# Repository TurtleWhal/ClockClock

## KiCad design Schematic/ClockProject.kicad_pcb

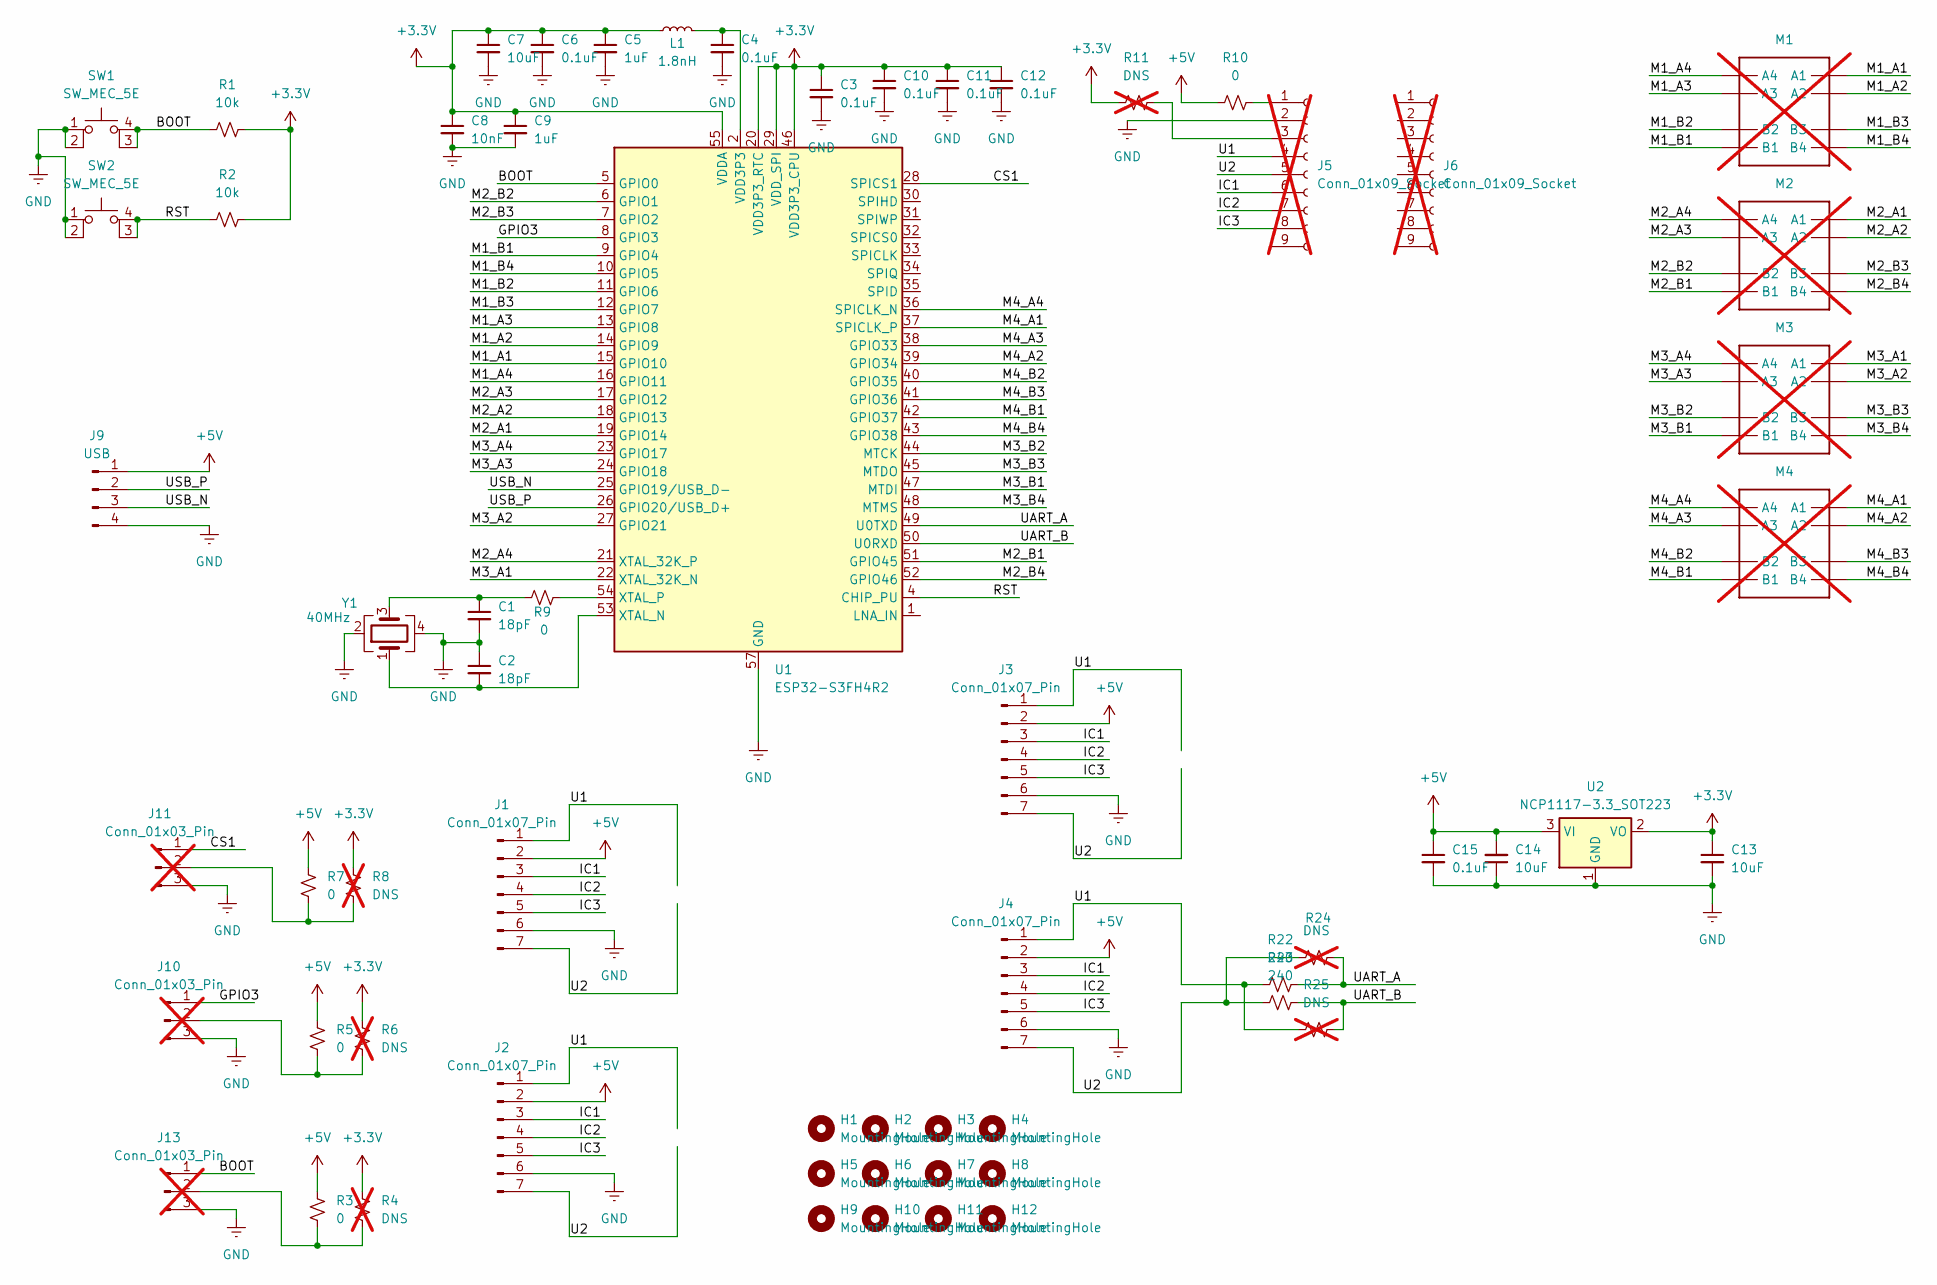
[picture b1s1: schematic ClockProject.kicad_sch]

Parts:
C1, C2: 18pF; C_0805_2012Metric; LCSC Part # C1797
C3, C4, C6, C10, C11, C12, C15: 0.1uF; C_0805_2012Metric; LCSC Part # C49678
C5, C9: 1uF; C_0805_2012Metric; LCSC Part # C28323
C7, C13, C14: 10uF; C_0805_2012Metric; LCSC Part # C15850
C8: 10nF; C_0805_2012Metric; LCSC Part # C1710
H1, H2, H3, H4, H5, H6, H7, H8, H9, H10, H11, H12: MountingHole; MountingHole_3.5mm
J1, J2: Conn_01x07_Pin; HDR-SMD_7P-P2.54-H-F-L11.5; LCSC Part # C5142240
J3, J4: Conn_01x07_Pin; HDR-SMD_7P-P2.54-H-F-L11.5-RIGHT; LCSC Part # C5142240
J5, J6: Conn_01x09_Socket; PinSocket_1x09_P2.54mm_Vertical; not fitted
J9: USB; PinHeader_1x04_P2.54mm_Vertical_SMD_Pin1Right; LCSC Part # C2984276
J10, J11, J13: Conn_01x03_Pin; PinSocket_1x03_P2.54mm_Vertical; not fitted
L1: 1.8nH; L_0805_2012Metric; LCSC Part # C1036
M1, M2, M3, M4: VID28-05; not fitted
R1, R2: 10k; R_0805_2012Metric; LCSC Part # C17414
R3, R5, R7, R9, R10: 0; R_0805_2012Metric; LCSC Part # C17477
R4, R6, R8, R24, R25: DNS; R_0805_2012Metric; not fitted
R11: DNS; R_0805_2012Metric; LCSC Part # C17572; not fitted
R22, R23: 240; R_0805_2012Metric; LCSC Part # C17572
SW1, SW2: SW_MEC_5E; SW-SMD_4P-L5.1-W5.1-P3.70-LS6.5-TL_H1.5; LCSC Part # C318884
U1: ESP32-S3FH4R2; QFN56_S3FH4R2_EXP; LCSC Part # C3013940
U2: NCP1117-3.3_SOT223; SOT-223-3_TabPin2; LCSC Part # C6186
Y1: 40MHz; Crystal_SMD_TXC_7M-4Pin_3.2x2.5mm; LCSC Part # C19191260

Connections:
+3.3V: C3.1, C5.1, C6.1, C7.1, C8.1, C9.1, C10.1, C11.1, C12.1, C13.1, L1.1, R1.2, R2.2, R4.2, R6.2, R8.2, R11.2, U1.20 (VDD3P3_RTC), U1.29 (VDD_SPI), U1.46 (VDD3P3_CPU), U1.55 (VDDA), U1.56 (VDDA), U2.2 (VO)
+5V: C14.2, C15.1, J1.2, J2.2, J3.2, J4.2, J9.1, R3.2, R5.2, R7.2, R10.2, U2.3 (VI)
/BOOT: J13.1, R1.1, SW1.3 (K), SW1.4 (A), U1.5 (GPIO0)
/CS1: J11.1, U1.28 (SPICS1)
/GPIO3: J10.1, U1.8 (GPIO3)
/IC1: J1.3, J2.3, J3.3, J4.3, J5.6
/IC2: J1.4, J2.4, J3.4, J4.4, J5.7
/IC3: J1.5, J2.5, J3.5, J4.5, J5.8
/M1_A1: M1.A1, U1.15 (GPIO10)
/M1_A2: M1.A2, U1.14 (GPIO9)
/M1_A3: M1.A3, U1.13 (GPIO8)
/M1_A4: M1.A4, U1.16 (GPIO11)
/M1_B1: M1.B1, U1.9 (GPIO4)
/M1_B2: M1.B2, U1.11 (GPIO6)
/M1_B3: M1.B3, U1.12 (GPIO7)
/M1_B4: M1.B4, U1.10 (GPIO5)
/M2_A1: M2.A1, U1.19 (GPIO14)
/M2_A2: M2.A2, U1.18 (GPIO13)
/M2_A3: M2.A3, U1.17 (GPIO12)
/M2_A4: M2.A4, U1.21 (XTAL_32K_P)
/M2_B1: M2.B1, U1.51 (GPIO45)
/M2_B2: M2.B2, U1.6 (GPIO1)
/M2_B3: M2.B3, U1.7 (GPIO2)
/M2_B4: M2.B4, U1.52 (GPIO46)
/M3_A1: M3.A1, U1.22 (XTAL_32K_N)
/M3_A2: M3.A2, U1.27 (GPIO21)
/M3_A3: M3.A3, U1.24 (GPIO18)
/M3_A4: M3.A4, U1.23 (GPIO17)
/M3_B1: M3.B1, U1.47 (MTDI)
/M3_B2: M3.B2, U1.44 (MTCK)
/M3_B3: M3.B3, U1.45 (MTDO)
/M3_B4: M3.B4, U1.48 (MTMS)
/M4_A1: M4.A1, U1.37 (SPICLK_P)
/M4_A2: M4.A2, U1.39 (GPIO34)
/M4_A3: M4.A3, U1.38 (GPIO33)
/M4_A4: M4.A4, U1.36 (SPICLK_N)
/M4_B1: M4.B1, U1.42 (GPIO37)
/M4_B2: M4.B2, U1.40 (GPIO35)
/M4_B3: M4.B3, U1.41 (GPIO36)
/M4_B4: M4.B4, U1.43 (GPIO38)
/RST: R2.1, SW2.3 (K), SW2.4 (A), U1.4 (CHIP_PU)
/U1: J1.1, J2.1, J3.1, J4.1, J5.4, R22.2, R25.2
/U2: J1.7, J2.7, J3.7, J4.7, J5.5, R23.2, R24.2
/UART_A: R22.1, R24.1, U1.49 (U0TXD)
/UART_B: R23.1, R25.1, U1.50 (U0RXD)
/USB_N: J9.3, U1.25 (GPIO19/USB_D-)
/USB_P: J9.2, U1.26 (GPIO20/USB_D+)
GND: C1.2, C2.1, C3.2, C4.2, C5.2, C6.2, C7.2, C8.2, C9.2, C10.2, C11.2, C12.2, C13.2, C14.1, C15.2, J1.6, J2.6, J3.6, J4.6, J5.2, J9.4, J10.3, J11.3, J13.3, SW1.1, SW1.2, SW2.1, SW2.2, U1.57 (GND), U2.1 (GND), Y1.2, Y1.4
unnamed: C1.1, R9.2, Y1.3
unnamed: C4.1, L1.2, U1.2 (VDD3P3), U1.3 (VDD3P3)
unnamed: J5.1, R10.1
unnamed: J5.3, R11.1
unnamed: J10.2, R5.1, R6.1
unnamed: J11.2, R7.1, R8.1
unnamed: J13.2, R3.1, R4.1
unnamed: C2.2, U1.53 (XTAL_N), Y1.1
unnamed: R9.1, U1.54 (XTAL_P)

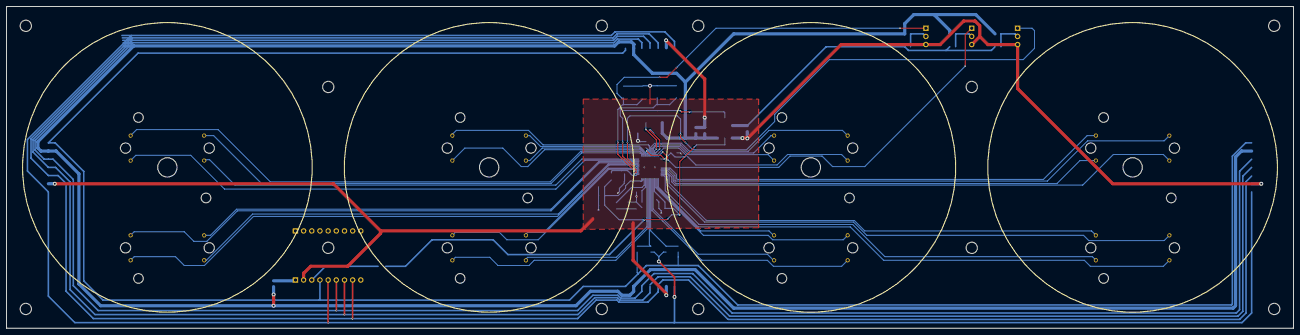
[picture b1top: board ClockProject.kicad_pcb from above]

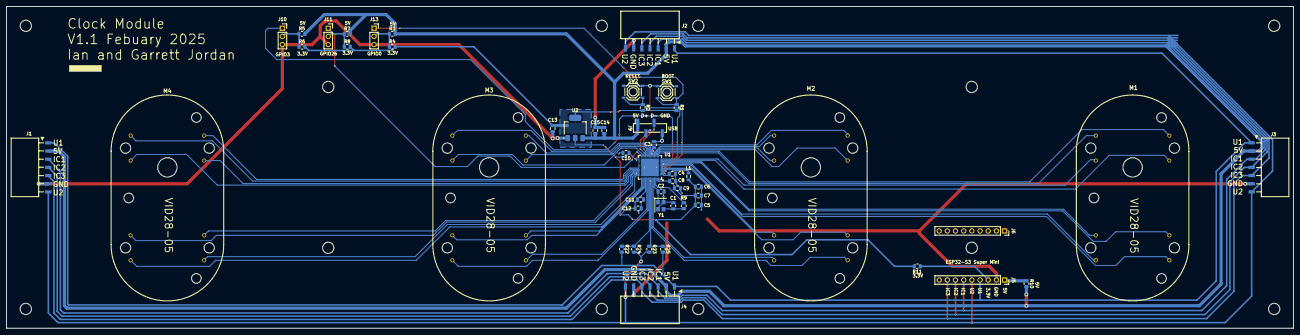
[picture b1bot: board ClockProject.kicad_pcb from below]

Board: 2 copper layers, 400.0 x 100.0 mm, 62 parts (50 on the bottom side), 57 nets.

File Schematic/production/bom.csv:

Designator,Footprint,Quantity,Value,LCSC Part #
"C1, C2",0805,2,18pF,C1797
"C10, C11, C12, C15, C3, C4, C6",0805,7,0.1uF,C49678
"C13, C14, C7",0805,3,10uF,C15850
"C5, C9",0805,2,1uF,C28323
C8,0805,1,10nF,C1710
"J1, J2",HDR-SMD_7P-P2.54-H-F-L11.5,2,Conn_01x07_Pin,C5142240
"J3, J4",HDR-SMD_7P-P2.54-H-F-L11.5-RIGHT,2,Conn_01x07_Pin,C5142240
J9,PinHeader_1x04_P2.54mm_Vertical_SMD_Pin1Right,1,USB,C2984276
L1,0805,1,1.8nH,C1036
"R1, R2",0805,2,10k,C17414
"R10, R3, R5, R7, R9",0805,5,0,C17477
"R22, R23",0805,2,240,C17572
"SW1, SW2",SW-SMD_4P-L5.1-W5.1-P3.70-LS6.5-TL_H1.5,2,SW_MEC_5E,C318884
U1,QFN56_S3FH4R2_EXP,1,ESP32-S3FH4R2,C3013940
U2,SOT-223-3_TabPin2,1,NCP1117-3.3_SOT223,C6186
Y1,Crystal_SMD_TXC_7M-4Pin_3.2x2.5mm,1,40MHz,C19191260

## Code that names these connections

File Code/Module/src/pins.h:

// Pinout from Table 2-4 in Datasheet

// ---- Motors ----

// Motor 1
#define M1_A1 10 // Pin 15
#define M1_A2 9  // Pin 14
#define M1_A3 8  // Pin 13
#define M1_A4 11 // Pin 16
#define M1_B1 4  // Pin 9
#define M1_B2 6  // Pin 11
#define M1_B3 7  // Pin 12
#define M1_B4 5  // Pin 10

// Motor 2
#define M2_A1 14 // Pin 19
#define M2_A2 13 // Pin 18
#define M2_A3 12 // Pin 17
#define M2_A4 15 // Pin 20
#define M2_B1 45 // Pin 51
#define M2_B2 1  // Pin 6
#define M2_B3 2  // Pin 7
#define M2_B4 46 // Pin 52

// Motor 3
#define M3_A1 16 // Pin 22
#define M3_A2 21 // Pin 27
#define M3_A3 18 // Pin 24
#define M3_A4 17 // Pin 23
#define M3_B1 41 // Pin 47
#define M3_B2 39 // Pin 44
#define M3_B3 40 // Pin 45
#define M3_B4 42 // Pin 48

// Motor 4
#define M4_A1 47 // Pin 37
#define M4_A2 34 // Pin 39
#define M4_A3 33 // Pin 38
#define M4_A4 48 // Pin 36
#define M4_B1 37 // Pin 42
#define M4_B2 35 // Pin 40
#define M4_B3 36 // Pin 41
#define M4_B4 38 // Pin 43

// ---- Headers ----

#define HEADER_1 3  // Header 1 (J10, GPIO3, Pin 8)
#define HEADER_2 26 // Header 2 (J11, CS1, Pin 28)
#define HEADER_3 0  // Header 3 (J13, BOOT, Pin 5)

// ---- Buttons ----
#define BUTTON_BOOT 0 // Boot Button (Pin 5)

// ---- UART ----
#define UART_A 43 // Pin 49
#define UART_B 44 // Pin 50

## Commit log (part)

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2025-02-24 Added schematic and pins.h
2025-02-25 Fixed multiple initial issues
    Fixed Silk for Connectors (GND move)
    Fixed Boot/Reset Silk
    Moved Edge Connectors closer to edge
2025-02-27 some initial code (not tested)
2025-02-27 working with timers
2025-02-27 added acceleration and deceleration
2025-02-27 Microstepping theoretically working
2025-02-27 changed analogwritefrequency
2025-03-01 Microstepping working
2025-03-02 hand cad and microstepping actrually working
2025-03-02 testing
2025-03-02 some stuff
2025-03-03 Serial Working, data struct not
2025-03-13 clock serial working well as library
2025-03-13 added serial timeout and clock buffer
2025-03-13 added font and drawing code
2025-03-13 added web server
2025-03-14 web page working and sending hands
2025-03-14 added shadow to webpage
2025-03-14 added firmware upload
2025-03-16 arduino 3.0.0 and serial basically working
2025-04-06 fixed crashing after some time (memory leak)
2025-04-06 sending buffer working
2025-04-06 Serial communication working across all modules
2025-04-07 added start of code for firmware uploading
2025-04-07 tried some stuff
2025-04-08 Before PSRAM Try
2025-04-08 PSRAM Working
2025-04-08 PSRAM buffer working, storage working, OTA not working
2025-04-08 OTA WORKING!!
2025-04-08 Cleaned up code, added versioning
2025-04-08 Minor code cleanup
2025-04-08 Cleaned code
2025-04-08 Bit of polish on master
2025-04-08 Clean Up
2025-04-08 Added versions to master, auto zero before upload
2025-04-09 No SPIFFS! Fast. Better debug code.
2025-04-09 FIRMWARE UPDATES WORKINGGGGGG!!!!!
2025-04-11 added set speed option
2025-04-13 fixed micros rollover
2025-04-13 steppers working way better
2025-05-15 added custom text option
2025-05-16 added all font characters
2025-06-02 stepper code ish
2025-06-18 motor control working with acceleration and time
2025-06-18 converted motor control api to degrees
2025-06-18 added favicon to webpage
2025-06-19 added interactive hands
2025-06-19 motor directions working
2025-06-19 added array of values
2025-06-19 microstepping kinda working
2025-06-20 microstepping working slowly
2025-06-21 Microstep test working with step table
2025-06-22 Working Software PWM on 16 channels
    dirty code
2025-06-22 Cleaned up comments
2025-06-22 Microstepping working with Motor Control code
2025-11-24 Full Clock Working
2025-11-28 Animations and transitions working well
2025-11-28 Added lowercase font
2025-11-29 PSRAM firmware updating and cycle mode
2026-06-14 QOL Changes
2026-06-22 Better PWM + Animation Timing
